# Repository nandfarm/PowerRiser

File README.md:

# PowerRiser – Lenovo Tiny 5 PCIe & NVMe Riser Board

</br>

# Buy preassembled boards:

Best for European locations (EUR currency):</br>

Best for International locations (USD currency):</br>

# PowerRiser Board

PowerRiser is a custom-designed passive riser board that allows you to break out the proprietary Lenovo Tiny 5 series PCIe connector into a standard open-ended x8 PCIe slot, while also providing an additional M.2 NVMe slot (2230/2242 sizes only) for further storage expansion. This board was specifically designed for select Lenovo Tiny 5 series systems (8th/9th gen), such as:

- ThinkCentre M720q

- ThinkCentre M920q

- ThinkCentre M920x

- ThinkStation P330 Tiny

These boards are compatible with the following Levono riser FRU codes: 01AJ940, 01AJ902, 01AJ929. Basically if you are looking for any of the risers with the FRU codes mentioned above, this riser will do the same job and will allow you access to an extra 4 lane NVMe M.2 2230 or 2242 slot.

⚠ Please note: The additional M.2 slot supports only PCIe NVMe drives, not SATA drives.

## Background
This project is inspired by the [TinyRiser](https://github.com/a-little-wifi/Tinyriser)  board originally designed by [WifiCable](https://x.com/wificable_). After building a batch of [TinyRisers](https://github.com/a-little-wifi/Tinyriser) for personal use and realizing some of my Lenovo Tiny systems had clearance issues (due to the WiFi/BT expansion boards), I decided to create my own variant — which I now call PowerRiser. If you are considering using 2260 or 2280 (with caution) NVMEs, please connect with [WifiCable](https://x.com/wificable_) for details on how to acquire the [TinyRiser](https://github.com/a-little-wifi/Tinyriser).

PowerRiser was developed to:

- Avoid clearance conflicts with other expansion boards.

- Allow installation of short NVMe drives (2230/2242) without obstruction.

- Provide an open-ended x8 PCIe connector that can accept longer x16 PCIe cards (electrically still x8).

Physically, the only modification required is removing the front metal bracket that holds the Bluetooth antenna. (Please refer to the photos in the repo for installation examples, including with an x16 graphics card installed.)

## Usage & Limitations
You can safely install longer PCIe cards (x16), but electrically the slot remains x8.

NVMe drives supported: 2230 and 2242 sizes only.

This riser is only compatible with the Lenovo Tiny 5 series models listed above.

SATA M.2 drives are not supported on the added M.2 slot.

The riser is cabable of accepting x16 PCIe boards but in order for them to be detected, the "PCIe_Detect" solder bridge on the back needs to be bridged.

</br>

## Project Origin & Intent
This project was built from personal need, trial, and experimentation and so far I have built about 20 boards for my own setups and for others. I hope it helps others facing the same limitations with their Lenovo Tiny builds.

## License
This project is licensed under the CERN Open Hardware License v2 - Strongly Reciprocal (CERN-OHL-S).

You are free to:

 - Manufacture and assemble this board.

- Use it in your own projects.

- Modify and improve it.

However, any modifications and derived works must also be distributed under the same license.

For full license terms, please refer to [CERN-OHL-S](https://ohwr.org/project/cernohl/wikis/home).

## Reports from buyers

As some amy know I have sent a mass email to everyone who bought this board to ask what drive they are using and if they had issues with them. So many replies! Thank you all for the support. Below is the list with everything I received. I will update it as things come in. Keep in mind that this is not an exhaustive list. There are many moderls of drives out there and all should be compatible. If you do find anything let me know!

SSDs reported OK:

- Crucial P310 2230 1TB

- Sabrent Rocket 2230 1TB (SB-2130-1TB)

- Kingston NV3 2230-SNV3SM3/1T0

- WD Black SN770M 2000 GB M.2 2230

- Corsair MP600 Micro 2TB

- Intel DC P3605 1.6TB

- Micron 2400 Series MTFDKBK256TGE 256GB

- ADATA Legend 710 256GB

- Intel Optane M10 MEMPEK1J016GAH 16GB

Issues reported:

- SK Hynix 2230 PVC10 1TB -> reported as not detected at all

- SK Hynix 2230 BC711 512GB -> works but ASPM needs to be turned off in bios, or disable the L1.1 and L1.2 substates in the OS.

- Micron 2400 Series MTFDKCD1T0QFM 1TB -> gets detected at Windows startup but then dissapears. Probably also a ASPM related issue but no further tests were made.

## Disclaimer
⚠ Use at your own risk.
By using, manufacturing, or assembling this board, you accept that:

I am not responsible for any damages, whether physical, financial, or mental, arising from its use.

The design has been made available for educational, experimental, and hobbyist purposes.

Always double-check compatibility, power requirements, and mechanical fit before installation.

## Project Links

Tindie Listing (if you wish to purchase a pre-assembled unit): [PowerRiser on Tindie](https://www.tindie.com/products/nandfarm/powerriser-by-nandfarm/)

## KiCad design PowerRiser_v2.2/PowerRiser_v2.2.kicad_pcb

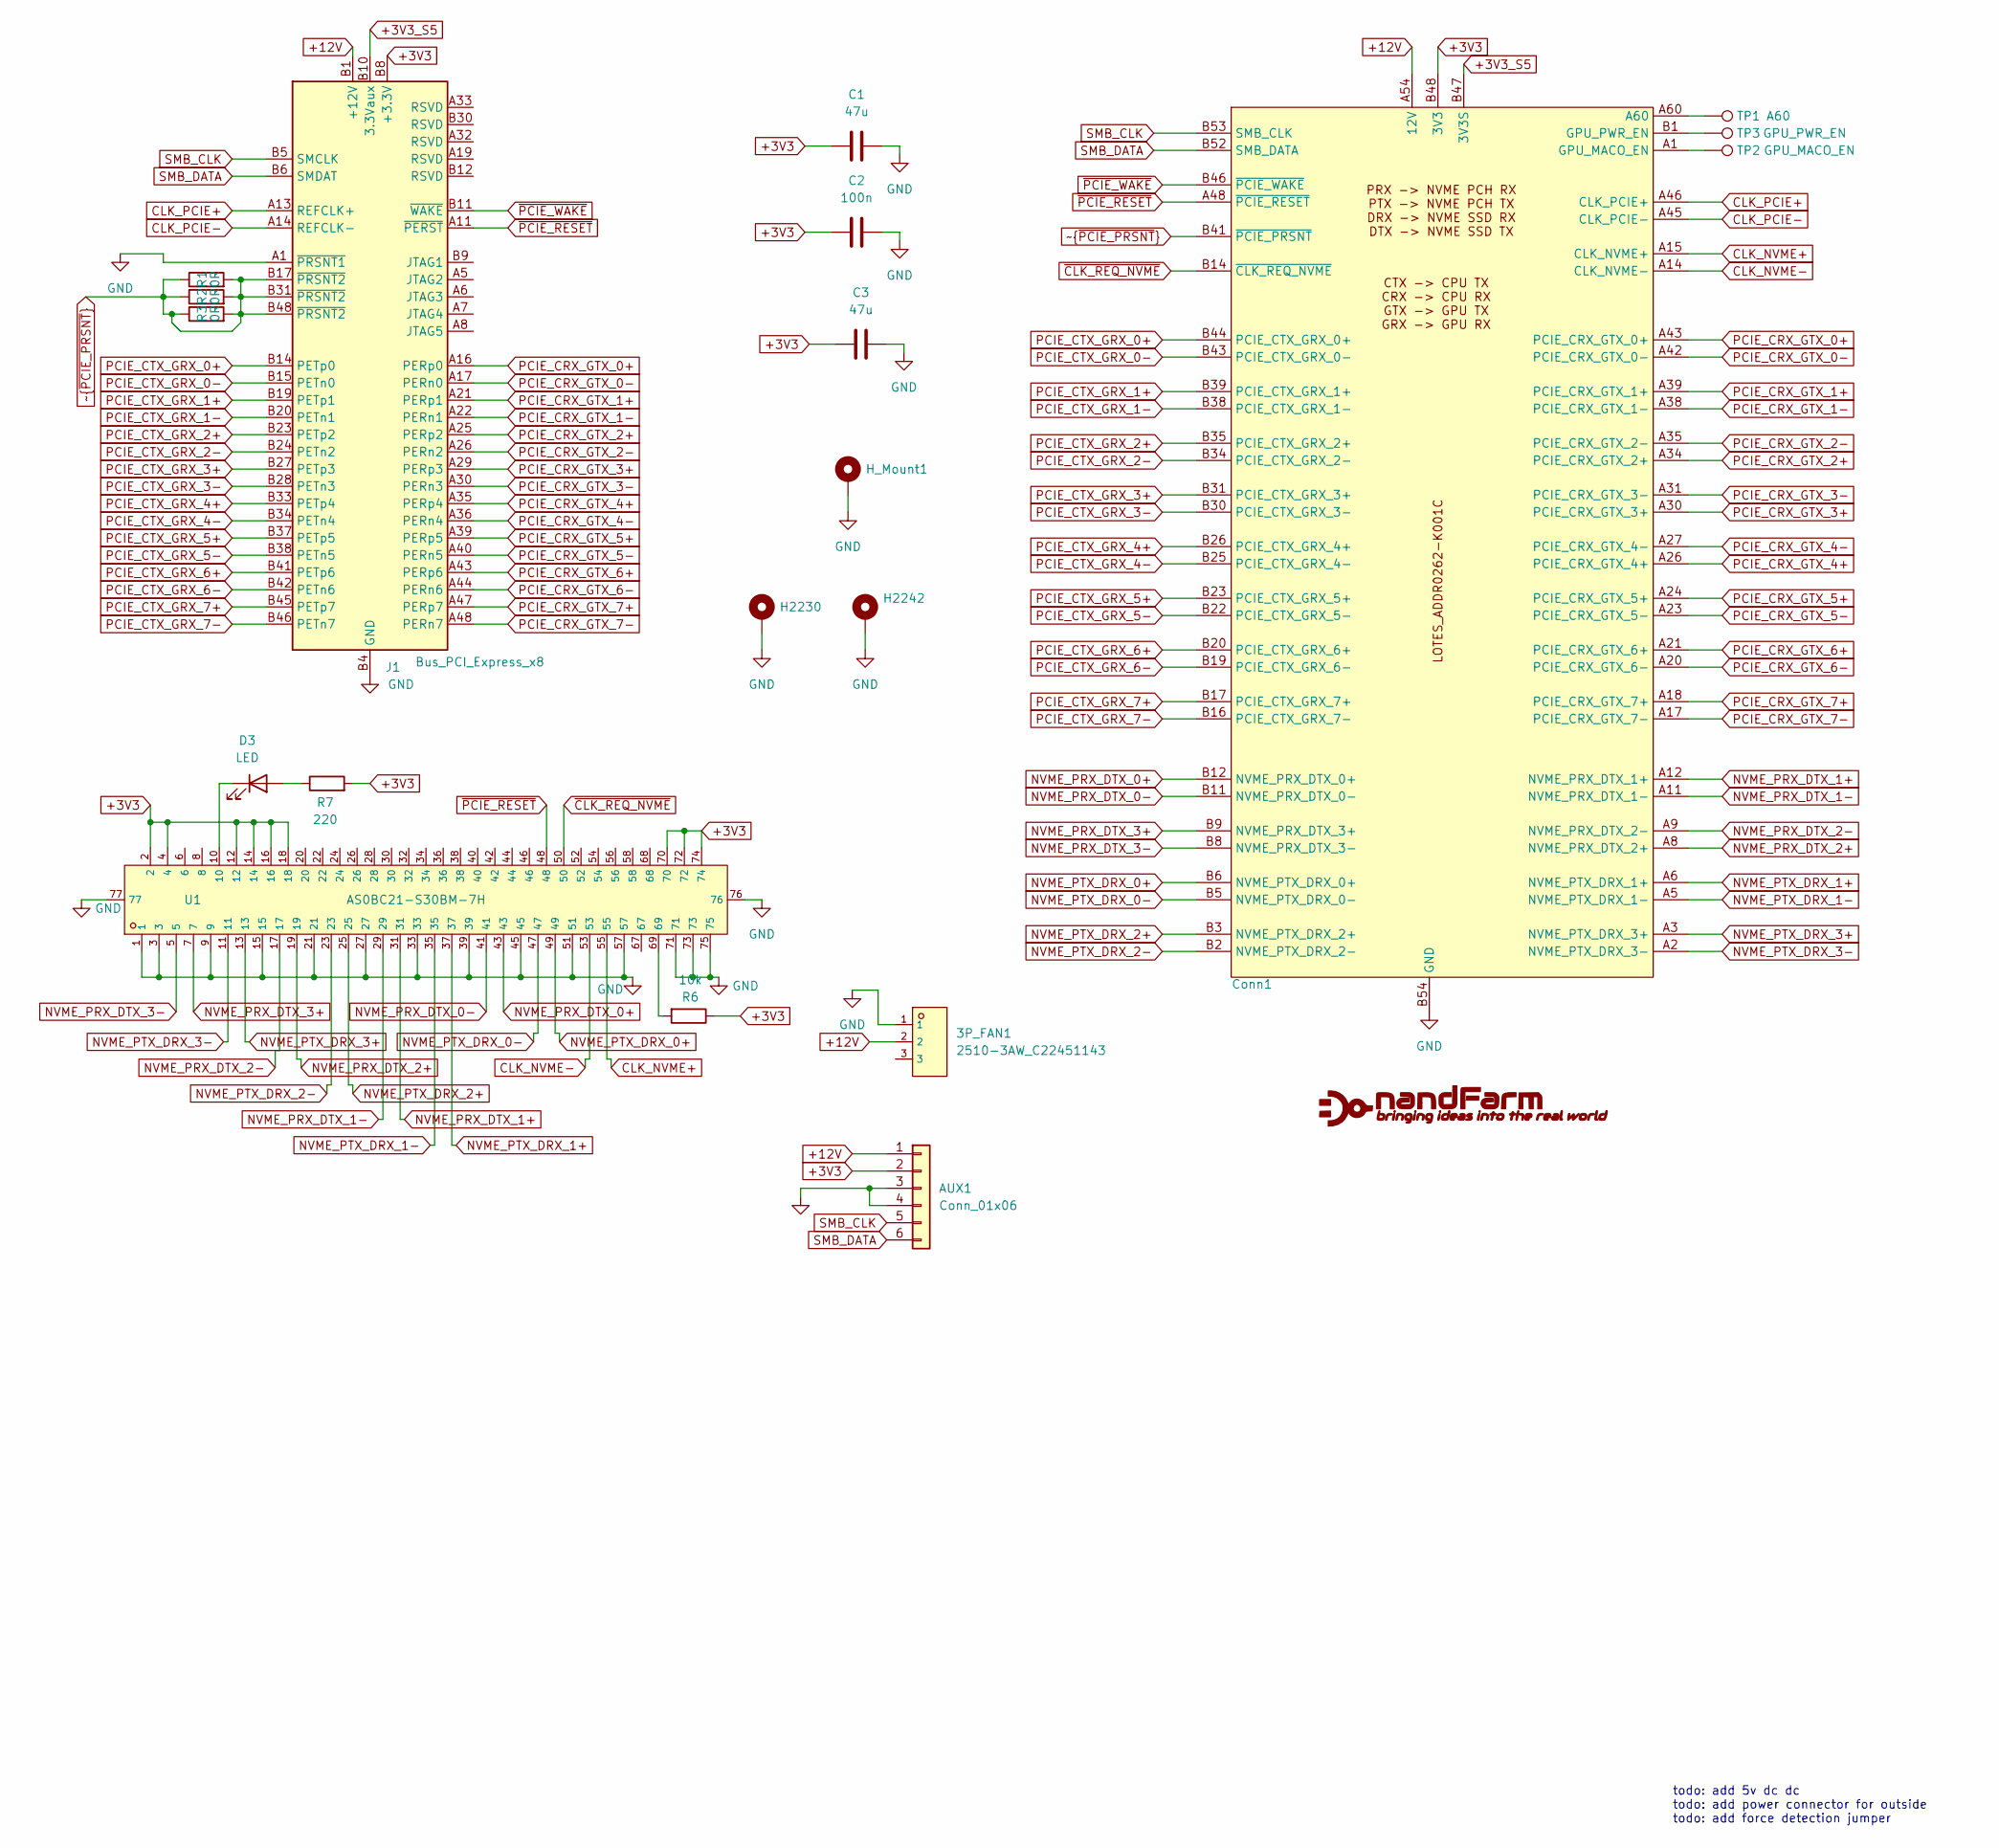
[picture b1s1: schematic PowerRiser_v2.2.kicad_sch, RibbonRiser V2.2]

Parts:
3P_FAN1: 2510-3AW_C22451143; CONN-TH_2510-3AW; LCSC C22451143
AUX1: Conn_01x06; PinHeader_1x06_P2.54mm_Vertical
C1, C3: 47u; C_1206_3216Metric_Pad1.33x1.80mm_HandSolder
C2: 100n; C_0805_2012Metric_Pad1.18x1.45mm_HandSolder
Conn1: Mx20qx_PCIe_FP
D3: LED; LED_0805_2012Metric
H2230, H2242: MountingHole_Pad; MountingHole_4.3mm_M4_ISO7380_Pad_TopOnly
H_Mount1: MountingHole_Pad; MountingHole_4.3mm_M4_ISO7380_Pad_TopOnly
J1: Bus_PCI_Express_x8; CONN-TH_98P-P1.00-V_3183-XXXXXPXT
R1, R2, R3: 0R; R_0603_1608Metric_Pad0.98x0.95mm_HandSolder
R6: 10k; R_0805_2012Metric
R7: 220; R_0805_2012Metric
TP1: A60; TestPoint_Pad_D1.0mm
TP2: GPU_MACO_EN; TestPoint_Pad_D1.0mm
TP3: GPU_PWR_EN; TestPoint_Pad_D1.0mm
U1: AS0BC21-S30BM-7H; CONN-SMD_AS0BC21-S30BM-7H; LCSC C2832351

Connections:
+3V3: AUX1.2, C1.1, C2.1, C3.1, Conn1.A51 (3V3), Conn1.A52 (3V3), Conn1.A53 (3V3), Conn1.B48 (3V3), Conn1.B49 (3V3), Conn1.B50 (3V3), J1.A9 (+3.3V), J1.A10 (+3.3V), J1.B8 (+3.3V), R6.1, R7.2, U1.2, U1.4, U1.12, U1.14, U1.16, U1.18, U1.70, U1.72, U1.74
+3V3_S5: Conn1.A50 (3V3S), Conn1.B47 (3V3S), J1.B10 (3.3Vaux)
+12V: 3P_FAN1.2, AUX1.1, Conn1.A54 (12V), Conn1.A55 (12V), Conn1.A56 (12V), Conn1.A57 (12V), Conn1.A58 (12V), Conn1.A59 (12V), Conn1.B55 (12V), Conn1.B56 (12V), Conn1.B57 (12V), Conn1.B58 (12V), Conn1.B59 (12V), Conn1.B60 (12V), J1.A2 (+12V), J1.A3 (+12V), J1.B1 (+12V), J1.B2 (+12V), J1.B3 (+12V); also elsewhere on the board
CLK_NVME+: Conn1.A15 (CLK_NVME+), U1.55
CLK_NVME-: Conn1.A14 (CLK_NVME-), U1.53
CLK_PCIE+: Conn1.A46 (CLK_PCIE+), J1.A13 (REFCLK+)
CLK_PCIE-: Conn1.A45 (CLK_PCIE-), J1.A14 (REFCLK-)
GND: 3P_FAN1.1, AUX1.3, AUX1.4, C1.2, C2.2, C3.2, Conn1.A4 (GND), Conn1.A7 (GND), Conn1.A10 (GND), Conn1.A13 (GND), Conn1.A16 (GND), Conn1.A19 (GND), Conn1.A22 (GND), Conn1.A25 (GND), Conn1.A28 (GND), Conn1.A29 (GND), Conn1.A32 (GND), Conn1.A33 (GND), Conn1.A36 (GND), Conn1.A37 (GND), Conn1.A40 (GND), Conn1.A41 (GND), Conn1.A44 (GND), Conn1.A47 (GND), Conn1.A49 (GND), Conn1.B4 (GND), Conn1.B7 (GND), Conn1.B10 (GND), Conn1.B13 (GND), Conn1.B15 (GND), Conn1.B18 (GND), Conn1.B21 (GND), Conn1.B24 (GND), Conn1.B27 (GND), Conn1.B29 (GND), Conn1.B32 (GND), Conn1.B33 (GND), Conn1.B36 (GND), Conn1.B37 (GND), Conn1.B40 (GND), Conn1.B42 (GND), Conn1.B45 (GND), Conn1.B51 (GND), Conn1.B54 (GND), H2230.1, H2242.1, H_Mount1.1, J1.A1 (~PRSNT1), J1.A4 (GND), J1.A12 (GND), J1.A15 (GND), J1.A18 (GND), J1.A20 (GND), J1.A23 (GND), J1.A24 (GND), J1.A27 (GND), J1.A28 (GND), J1.A31 (GND), J1.A34 (GND), J1.A37 (GND), J1.A38 (GND), J1.A41 (GND), J1.A42 (GND), J1.A45 (GND), J1.A46 (GND), J1.A49 (GND), J1.B4 (GND), J1.B7 (GND), J1.B13 (GND), J1.B16 (GND), J1.B18 (GND), J1.B21 (GND), J1.B22 (GND), J1.B25 (GND), J1.B26 (GND), J1.B29 (GND), J1.B32 (GND), J1.B35 (GND), J1.B36 (GND), J1.B39 (GND), J1.B40 (GND), J1.B43 (GND), J1.B44 (GND), J1.B47 (GND), J1.B49 (GND), U1.1, U1.3, U1.9, U1.15, U1.21, U1.27, U1.33, U1.39, U1.45, U1.51, U1.57, U1.71, U1.73, U1.75, U1.76, U1.77; also elsewhere on the board
NVME_PRX_DTX_0+: Conn1.B12 (NVME_PRX_DTX_0+), U1.43
NVME_PRX_DTX_0-: Conn1.B11 (NVME_PRX_DTX_0-), U1.41
NVME_PRX_DTX_1+: Conn1.A12 (NVME_PRX_DTX_1+), U1.31
NVME_PRX_DTX_1-: Conn1.A11 (NVME_PRX_DTX_1-), U1.29
NVME_PRX_DTX_2+: Conn1.A8 (NVME_PRX_DTX_2+), U1.19
NVME_PRX_DTX_2-: Conn1.A9 (NVME_PRX_DTX_2-), U1.17
NVME_PRX_DTX_3+: Conn1.B9 (NVME_PRX_DTX_3+), U1.7
NVME_PRX_DTX_3-: Conn1.B8 (NVME_PRX_DTX_3-), U1.5
NVME_PTX_DRX_0+: Conn1.B6 (NVME_PTX_DRX_0+), U1.49
NVME_PTX_DRX_0-: Conn1.B5 (NVME_PTX_DRX_0-), U1.47
NVME_PTX_DRX_1+: Conn1.A6 (NVME_PTX_DRX_1+), U1.37
NVME_PTX_DRX_1-: Conn1.A5 (NVME_PTX_DRX_1-), U1.35
NVME_PTX_DRX_2+: Conn1.B3 (NVME_PTX_DRX_2+), U1.25
NVME_PTX_DRX_2-: Conn1.B2 (NVME_PTX_DRX_2-), U1.23
NVME_PTX_DRX_3+: Conn1.A3 (NVME_PTX_DRX_3+), U1.13
NVME_PTX_DRX_3-: Conn1.A2 (NVME_PTX_DRX_3-), U1.11
unnamed: Conn1.A1 (GPU_MACO_EN), TP2.1
unnamed: Conn1.B1 (GPU_PWR_EN), TP3.1
unnamed: Conn1.A60, TP1.1
unnamed: D3.2 (A), R7.1
unnamed: D3.1 (K), U1.10
unnamed: R6.2, U1.69
PCIE_CRX_GTX_0+: Conn1.A43 (PCIE_CRX_GTX_0+), J1.A16 (PERp0)
PCIE_CRX_GTX_0-: Conn1.A42 (PCIE_CRX_GTX_0-), J1.A17 (PERn0)
PCIE_CRX_GTX_1+: Conn1.A39 (PCIE_CRX_GTX_1+), J1.A21 (PERp1)
PCIE_CRX_GTX_1-: Conn1.A38 (PCIE_CRX_GTX_1-), J1.A22 (PERn1)
PCIE_CRX_GTX_2+: Conn1.A34 (PCIE_CRX_GTX_2+), J1.A25 (PERp2)
PCIE_CRX_GTX_2-: Conn1.A35 (PCIE_CRX_GTX_2-), J1.A26 (PERn2)
PCIE_CRX_GTX_3+: Conn1.A30 (PCIE_CRX_GTX_3+), J1.A29 (PERp3)
PCIE_CRX_GTX_3-: Conn1.A31 (PCIE_CRX_GTX_3-), J1.A30 (PERn3)
PCIE_CRX_GTX_4+: Conn1.A26 (PCIE_CRX_GTX_4+), J1.A35 (PERp4)
PCIE_CRX_GTX_4-: Conn1.A27 (PCIE_CRX_GTX_4-), J1.A36 (PERn4)
PCIE_CRX_GTX_5+: Conn1.A24 (PCIE_CRX_GTX_5+), J1.A39 (PERp5)
PCIE_CRX_GTX_5-: Conn1.A23 (PCIE_CRX_GTX_5-), J1.A40 (PERn5)
PCIE_CRX_GTX_6+: Conn1.A21 (PCIE_CRX_GTX_6+), J1.A43 (PERp6)
PCIE_CRX_GTX_6-: Conn1.A20 (PCIE_CRX_GTX_6-), J1.A44 (PERn6)
PCIE_CRX_GTX_7+: Conn1.A18 (PCIE_CRX_GTX_7+), J1.A47 (PERp7)
PCIE_CRX_GTX_7-: Conn1.A17 (PCIE_CRX_GTX_7-), J1.A48 (PERn7)
PCIE_CTX_GRX_0+: Conn1.B44 (PCIE_CTX_GRX_0+), J1.B14 (PETp0)
PCIE_CTX_GRX_0-: Conn1.B43 (PCIE_CTX_GRX_0-), J1.B15 (PETn0)
PCIE_CTX_GRX_1+: Conn1.B39 (PCIE_CTX_GRX_1+), J1.B19 (PETp1)
PCIE_CTX_GRX_1-: Conn1.B38 (PCIE_CTX_GRX_1-), J1.B20 (PETn1)
PCIE_CTX_GRX_2+: Conn1.B35 (PCIE_CTX_GRX_2+), J1.B23 (PETp2)
PCIE_CTX_GRX_2-: Conn1.B34 (PCIE_CTX_GRX_2-), J1.B24 (PETn2)
PCIE_CTX_GRX_3+: Conn1.B31 (PCIE_CTX_GRX_3+), J1.B27 (PETp3)
PCIE_CTX_GRX_3-: Conn1.B30 (PCIE_CTX_GRX_3-), J1.B28 (PETn3)
PCIE_CTX_GRX_4+: Conn1.B26 (PCIE_CTX_GRX_4+), J1.B33 (PETp4)
PCIE_CTX_GRX_4-: Conn1.B25 (PCIE_CTX_GRX_4-), J1.B34 (PETn4)
PCIE_CTX_GRX_5+: Conn1.B23 (PCIE_CTX_GRX_5+), J1.B37 (PETp5)
PCIE_CTX_GRX_5-: Conn1.B22 (PCIE_CTX_GRX_5-), J1.B38 (PETn5)
PCIE_CTX_GRX_6+: Conn1.B20 (PCIE_CTX_GRX_6+), J1.B41 (PETp6)
PCIE_CTX_GRX_6-: Conn1.B19 (PCIE_CTX_GRX_6-), J1.B42 (PETn6)
PCIE_CTX_GRX_7+: Conn1.B17 (PCIE_CTX_GRX_7+), J1.B45 (PETp7)
PCIE_CTX_GRX_7-: Conn1.B16 (PCIE_CTX_GRX_7-), J1.B46 (PETn7)
SMB_CLK: AUX1.5, Conn1.B53 (SMB_CLK), J1.B5 (SMCLK)
SMB_DATA: AUX1.6, Conn1.B52 (SMB_DATA), J1.B6 (SMDAT)
~CLK_REQ_NVME: Conn1.B14 (~CLK_REQ_NVME), U1.50
~PCIE_RESET: Conn1.A48 (~PCIE_RESET), J1.A11 (~PERST), U1.48
~PCIE_WAKE: Conn1.B46 (~PCIE_WAKE), J1.B11 (~WAKE)
~~{PCIE_PRSNT}: Conn1.B28 (~PCIE_PRSNT), Conn1.B41 (~PCIE_PRSNT), J1.B17 (~PRSNT2), J1.B31 (~PRSNT2), J1.B48 (~PRSNT2), R1.1, R1.2, R2.1, R2.2, R3.1, R3.2

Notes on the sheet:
todo: add 5v dc dc todo: add power connector for outside todo: add force detection jumper

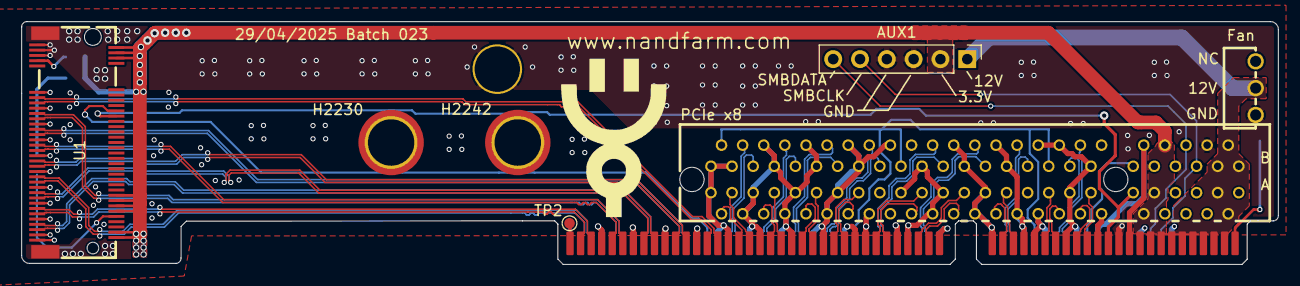
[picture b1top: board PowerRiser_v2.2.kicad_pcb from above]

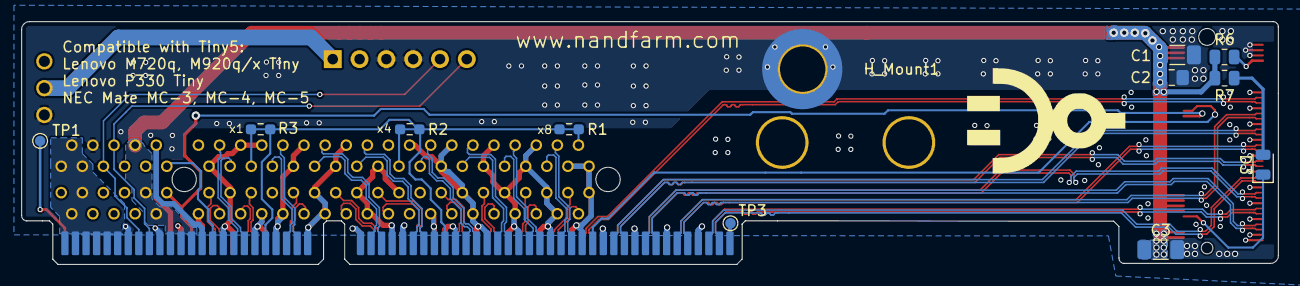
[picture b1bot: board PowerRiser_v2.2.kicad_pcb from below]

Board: 4 copper layers, 119.0 x 23.0 mm, 20 parts (12 on the bottom side), 68 nets.

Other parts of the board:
Fan: 2510-3AW_C22451143; CONN-TH_2510-3AW

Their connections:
+12V: Fan.2; also elsewhere on the board
GND: Fan.1; also elsewhere on the board

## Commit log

2025-07-24 Update README.md
    Added link to store
2025-12-23 Add buyer reports section to README
    Added a section for buyer reports detailing compatible SSDs and issues encountered with specific models.
2026-04-18 Add links to selling platforms in README
2026-05-23 Update README with buying options and notes
    Added purchase links for preassembled boards and clarified M.2 slot compatibility.
2026-05-23 Add purchase links for preassembled PowerRiser boards
2026-05-23 tidying up names and readme
2026-05-23 Update README with Lenovo riser compatibility details
    Added compatibility information for Lenovo riser FRU codes and noted M.2 slot drive support.
